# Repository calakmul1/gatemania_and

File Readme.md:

## Gatemania AND

### Description
This circuit showcases the CD4081BE Quad AND Gate. The LED is on if all switches are on. Two AND gates check if Switch 1/Switch 2 and Switch 3/Switch 4 are on. The third AND gate checks if both outputs of the former AND gates are on. If yes, it switches the LED on.

### Components Used
- CD40801BE Quand AND Gate
- OS102011MS2QN1 Switches
- BS7 Coin 3V Battery Holder
- Red LED
- 6x Resistors 10K
- 1x Resistor 100R

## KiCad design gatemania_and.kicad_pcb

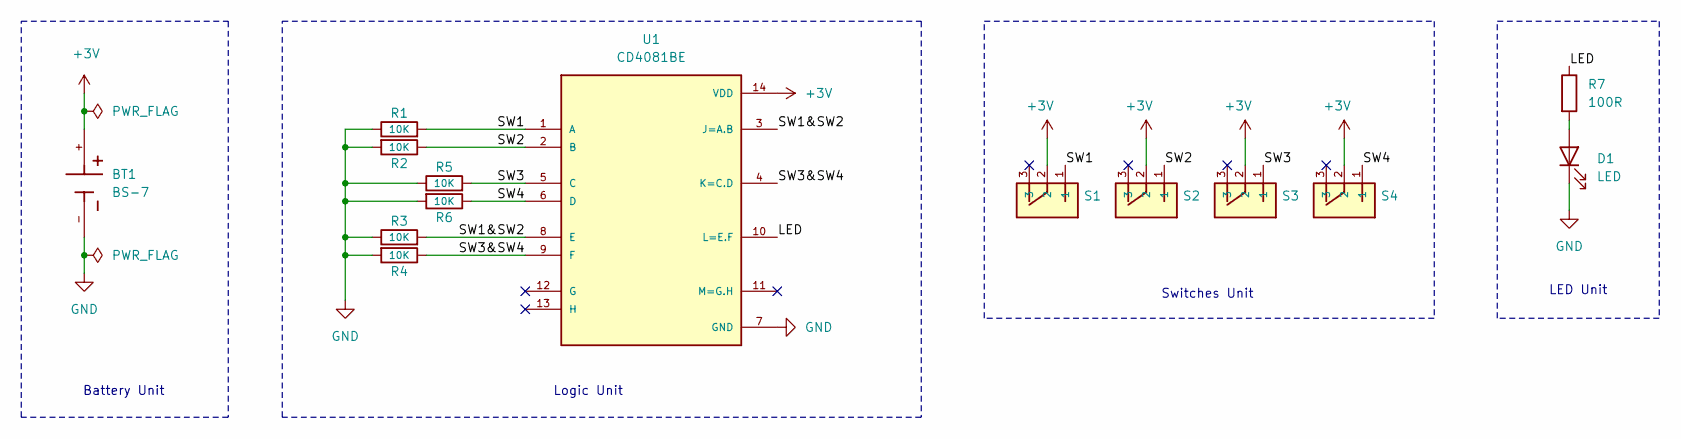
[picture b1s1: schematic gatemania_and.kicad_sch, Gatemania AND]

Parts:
BT1: BS-7
D1: LED; LED_D5.0mm
R1, R2, R3, R4, R5, R6: 10K; R_Axial_DIN0207_L6.3mm_D2.5mm_P15.24mm_Horizontal
R7: 100R; R_Axial_DIN0207_L6.3mm_D2.5mm_P15.24mm_Horizontal
S1, S2, S3, S4: OS102011MS2QN1
U1: CD4081BE

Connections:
+3V: BT1.+, S1.2, S2.2, S3.2, S4.2, U1.14 (VDD)
/LED: R7.1, U1.10 (L=E.F)
/SW1: R1.2, S1.1, U1.1 (A)
/SW1&SW2: R3.2, U1.3 (J=A.B), U1.8 (E)
/SW2: R2.1, S2.1, U1.2 (B)
/SW3: R5.2, S3.1, U1.5 (C)
/SW3&SW4: R4.1, U1.4 (K=C.D), U1.9 (F)
/SW4: R6.1, S4.1, U1.6 (D)
GND: BT1.-, D1.1 (K), R1.1, R2.2, R3.1, R4.2, R5.1, R6.2, U1.7 (GND)
unnamed: D1.2 (A), R7.2

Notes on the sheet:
Switches Unit
LED Unit
Logic Unit
Battery Unit

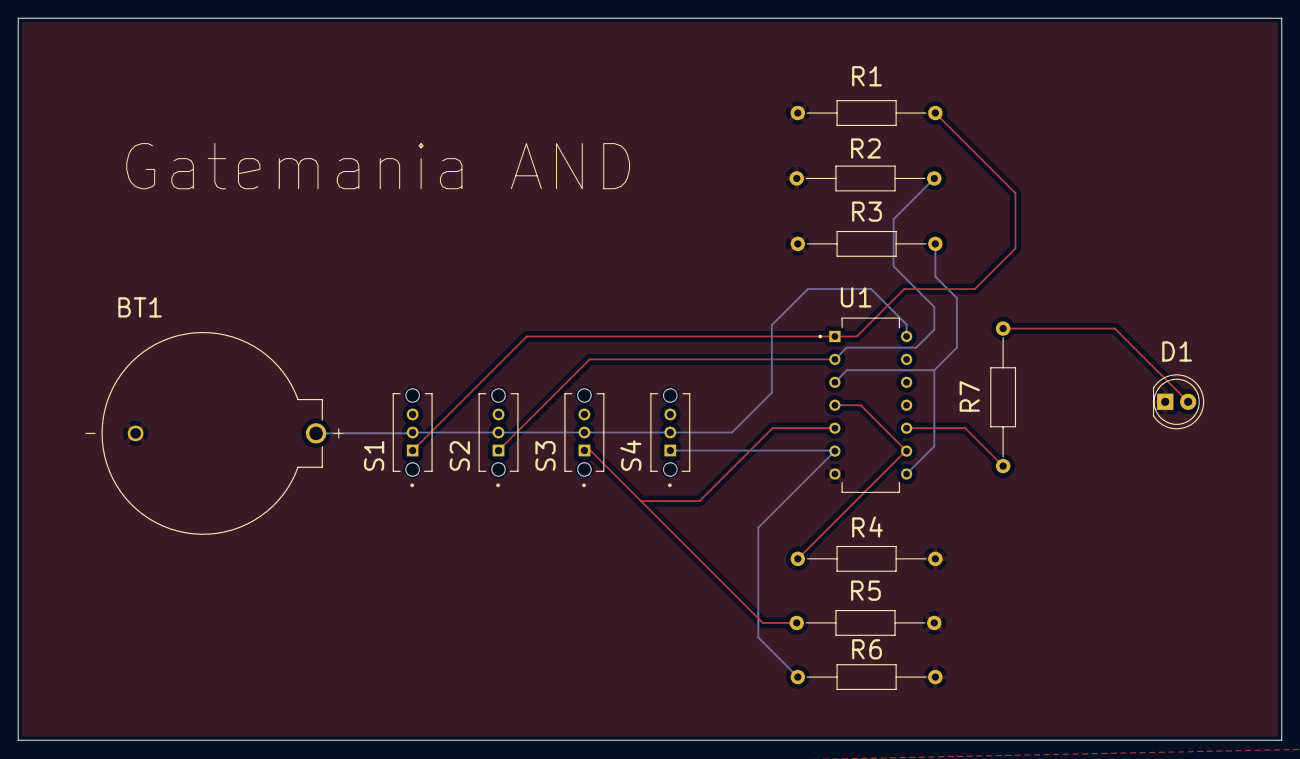
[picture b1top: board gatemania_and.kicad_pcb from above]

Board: 2 copper layers, 140.0 x 80.0 mm, 14 parts (0 on the bottom side), 10 nets.

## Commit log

2024-06-05 adding datasheets
2024-06-05 Adding schematics pdf and 3dview
2024-06-07 Add readme
2024-06-07 Remove backup zips from repo.
2024-06-07 check
2024-06-07 adding 3dview to readme
2024-06-07 adding license
2024-06-07 license modifications
2024-06-07 license
2024-06-07 remove bak
2024-06-07 adding attributes
